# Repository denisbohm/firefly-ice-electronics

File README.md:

firefly-ice-electronics
=======================

Firefly Ice Activity Monitor / Internet of Things Electronics

See http://fireflydesign.com for information on the open source Firefly Activity Monitor.

Copyright and License 
---------------------
Copyright 2013-2014 Firefly Design LLC / Denis Bohm

<br />This work is licensed under a <a rel="license" href="http://creativecommons.org/licenses/by/3.0/deed.en_US">Creative Commons Attribution 3.0 Unported License</a>.

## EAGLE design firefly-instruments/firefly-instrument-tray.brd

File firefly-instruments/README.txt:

Contact: Denis Bohm
denis@fireflydesign.com
(650) 814-1714

April 13h, 2017
Customer: Firefly Design, LLC
Board: Firefly Instrument Tray rev 0.5
Number of Layers: 2
Dimensions: 193 mm x 100 mm
PCB Thickness: 1.60 mm
ENIG
RoHS Compliant
Lead Free Processing

Files

firefly-instrument-tray.sch - Eagle 7 schematic file
firefly-instrument-tray.brd - Eagle 7 board file

firefly-instrument-tray-bom.xlsx - bill of materials
firefly-instrument-tray-schematic.pdf - schematic
firefly-instrument-tray-top-diagram.pdf - top (component) side assembly diagram
firefly-instrument-tray-centroid.csv - surface mount centroid placement data

Gerbers
firefly-instrument-tray.top - top (component) side
firefly-instrument-tray.bot - bottom side

firefly-instrument-tray.slk - top (component) side silk
firefly-instrument-tray.smt - top (component) side solder mask
firefly-instrument-tray.tsp - top (component) side stencil

firefly-instrument-tray.bsk - bottom side silk
firefly-instrument-tray.smb - bottom side solder mask
firefly-instrument-tray.bsp - bottom side stencil

firefly-instrument-tray.oln - outline

firefly-instrument-tray.drd - Excellon drill
firefly-instrument-tray.dri - tool list

Notes:
1) The design is done with Eagle 7.7.0 (files are of type sch, brd, and lib)..
2) Use Firefly Design BOM tool to generate the BOM from the schematic.
3) The tDocu & Document layers show all reference designators and orientation for assembly of the top side.
4) The bDocu shows all reference designators and orientation for assembly of the bottom side.
5) DRC rules and CAM setup are from Sunstone Circuits.  For CAM setup use _tsilk for top side silk and _bsilk for bottom side silk.
6) Centroid file generator is from Screaming Circuits.

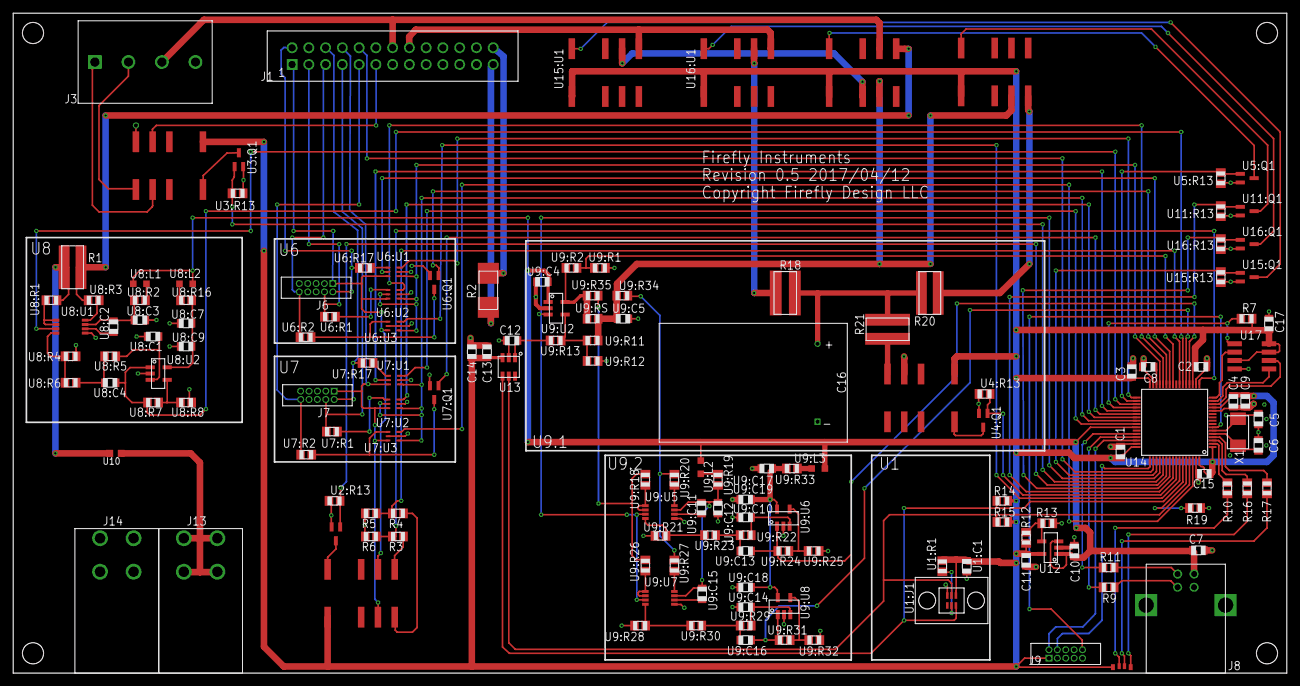
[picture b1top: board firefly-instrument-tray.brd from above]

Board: 2 copper layers, 193.0 x 100.0 mm, 153 parts (0 on the bottom side), 129 nets.

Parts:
C1, C2, C3, C12, C13, C15, C17: 100nF; C0805
C4, C10, C11: 1uF; C0805
C5, C6: 22pF; C0805
C7, C8: 4.7uF; C0805
C9: 10nF; C0805
C14: 10uF; C0805
C16: 1F; PM118
D1: LED-RGB-CAMSL0201RGB; MSL0201RGB
J1: CON-26; CON-HEADER-2X13
J3: CON-4282847-4; 282847-4
J6, J7, J9: CON-10SWD; SWD-10
J8: USB-4PINUSB-B1HSB6; USB-B1HSB6
J13, J14: CON-1CT3151; CT3151
R1: 0.1; KRL6432
R2: 100; RW0S6BB
R3, R4, R5, R6: 1k; R0805
R7: 10k; R0805
R9, R11: 22; R0805
R10, R16: 60; R0805
R12: 72.5k; R0805
R13: 10K; R0805
R14, R15: 4.7k; R0805
R17: 240; R0805
R18: 1 (2W WW); RCL1225
R19: 0; R0805
R20: 49.9 (2W WW); KRL6432
R21: 49.9 (2W WW); RCL1225
U1:C1, U8:C7, U9:C4, U9:C5, U9:C17: 1uF; C0805
U1:J1: SMFLP
U1:R1, U8:R5, U8:R6, U9:R22, U9:R23, U9:R29, U9:R30: 10k; R0805
U1:U1: TCS3471; DFN6
U2:Q1, U3:Q1, U4:Q1, U5:Q1, U6:Q1, U7:Q1, U11:Q1, U15:Q1, U16:Q1: FET-NMCPH3; MCPH3
U2:R13, U3:R13, U4:R13, U5:R13, U9:R28, U11:R13, U15:R13, U16:R13: 10K; R0805
U2:U1, U3:U1, U4:U1, U5:U1, U11:U1, U15:U1, U16:U1: TXS2SA
U6:R1, U6:R2, U6:R17, U7:R1, U7:R2, U7:R17: 240; R0805
U6:U1, U6:U2, U6:U3, U7:U1, U7:U2, U7:U3: 74LVCH1T45; SOT363
U8:C1, U8:C4, U9:C10, U9:C13, U9:C14, U9:C16: 1nF; C0805
U8:C2, U8:C9, U9:C11, U9:C15, U9:C18, U9:C19: 100nF; C0805
U8:C3, U9:C12: 10uF; C0805
U8:L1, U8:L2, U9:L2, U9:L3: 1k; L2012C
U8:R1, U9:R18: 1.8K; R0805
U8:R2, U9:R19, U9:R27, U9:R31, U9:R34, U9:R35: 0; R0805
U8:R3, U9:R20: 43; R0805
U8:R4, U9:R21: 12K; R0805
U8:R7, U9:R24: 376; R0805
U8:R8, U9:R25, U9:R32: 1K; R0805
U8:R16, U9:R33: 1; R0805
U8:U1, U9:U5, U9:U7: LTC6102-1MS8; MSOP8
U8:U2, U9:U6, U9:U8: TLV271SN2T1G; SOT-23-5
U9:R1, U9:R2, U9:R12, U9:R13: 100K; R0805
U9:R11: 650K; R0805
U9:R26, U9:RS: 4.7; R0805
U9:U2, U12: VREG-ADJAP7331-WG-7; SOT-23-5
U10: PTC0603; 0603
U13: MCP47X6; SOT-23-6
U14: STM32F411-LQFP64; LQFP-64
U17: MEMORY-SPISOA008; SOA008
X1: XTAL2CX5032GA; CX5032GA

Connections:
+3V3: C1.1, C2.1, C3.1, C4.1, C9.1, C11.1, C13.1, C14.1, C15.1, C17.1, D1.4, J9.1, R7.2, R12.2, R14.2, R15.2, U1:C1.1, U1:R1.2, U1:U1.1, U2:U1.1, U3:U1.1, U4:U1.1, U5:U1.1, U11:U1.1, U12.5, U13.3, U14.1, U14.13, U14.19, U14.32, U14.48, U14.64, U15:U1.1, U16:U1.1, U17.3, U17.7, U17.8
+5V: J13.1, J13.2, J13.3, J13.4, U10.1
ATE_BATTERY+2: U9:R1.2, U9:R2.1, U14.25
ATE_BAT_ADJ_EN: U14.51, U15:Q1.1, U15:R13.2
ATE_BAT_CAP_EN: U14.55, U16:Q1.1, U16:R13.2
ATE_BS_ADJ: C12.1, U9:R13.1, U13.1
ATE_BS_EN: U9:U2.3, U9:U5.3, U9:U7.3, U14.52
ATE_BS_SHR: U9:C13.1, U9:R24.2, U9:U6.1, U14.20
ATE_BS_SLR: U9:C16.1, U9:R31.2, U9:U8.1, U14.21
ATE_BUTTON_EN: U3:Q1.1, U3:R13.2, U14.53
ATE_DRAIN_EN: U4:Q1.1, U4:R13.2, U14.57
ATE_FILL_EN: U11:Q1.1, U11:R13.2, U14.56
ATE_MCU1_VCC2: R3.2, R6.1, U14.17
ATE_MCU2_VCC2: R4.2, R5.1, U14.23
ATE_MCU_VCC_SENSE: U2:Q1.1, U2:R13.2, U14.54
ATE_SCL: R15.1, U1:U1.2, U13.5, U14.61
ATE_SDA: R14.1, U1:U1.6, U13.4, U14.59
ATE_SWD1_DIR_TO_DUT: U6:U1.5, U14.26
ATE_SWD1_NRESET: U6:Q1.1, U14.27
ATE_SWD1_PWR: U6:U1.1, U6:U2.1, U6:U2.5, U6:U3.1, U14.29
ATE_SWD1_SENSE_NRESET: U6:U3.3, U14.58
ATE_SWD1_SWDCLK: U6:U2.3, U14.28
ATE_SWD1_SWDIO: U6:U1.3, U14.33
ATE_SWD2_DIR_TO_DUT: U7:U1.5, U14.37
ATE_SWD2_NRESET: U7:Q1.1, U14.38
ATE_SWD2_PWR: U7:U1.1, U7:U2.1, U7:U2.5, U7:U3.1, U14.40
ATE_SWD2_SENSE_NRESET: U7:U3.3, U14.62
ATE_SWD2_SWDCLK: U7:U2.3, U14.39
ATE_SWD2_SWDIO: U7:U1.3, U14.41
ATE_USB_5V_EN: U5:Q1.1, U5:R13.2, U14.34
ATE_USB_CS_EN: U8:U1.3, U14.35
ATE_USB_CS_OUT: U8:C4.1, U8:R7.2, U8:U2.1, U14.22
BATADJ: U5:U1.4, U9:C5.1, U9:R11.2, U9:R34.2, U9:RS.2, U11:U1.4
BATADJSAFE: U5:U1.3, U15:U1.9
BATCAP: R18.1, U16:U1.9
BOOT0: R19.1, U14.60
DRAINCAP: R21.1, U4:U1.5
DUT_BATTERY+: J1.16, U15:U1.8, U16:U1.8
DUT_BUTTON+: J1.11, U3:U1.4
DUT_MCU1_NRESET: J1.5, J6.10, U6:R2.2
DUT_MCU1_SWDCLK: J1.3, J6.4, U6:R1.2
DUT_MCU1_SWDIO: J1.2, J6.2, U6:R17.2
DUT_MCU1_VCC: J1.1, J6.1, U2:U1.9, U6:U1.6, U6:U2.6, U6:U3.6
DUT_MCU2_BOOT0: J1.10, U14.50
DUT_MCU2_NRESET: J1.9, J7.10, U7:R2.2
DUT_MCU2_SWDCLK: J1.7, J7.4, U7:R1.2
DUT_MCU2_SWDIO: J1.6, J7.2, U7:R17.2
DUT_MCU2_VCC: J1.8, J7.1, U2:U1.4, U7:U1.6, U7:U2.6, U7:U3.6
DUT_MOTOR+: J1.26, R2.1
DUT_MOTOR-: J1.25, R2.2
DUT_SWITCH_1: J3.1, U3:U1.9
DUT_SWITCH_2: J3.2, U3:U1.8
DUT_USB_5V: J1.14, J3.3, U5:U1.9
FILLCAP: R20.1, U11:U1.5
GND: C1.2, C2.2, C3.2, C4.2, C5.2, C6.2, C7.2, C8.2, C9.2, C10.2, C11.2, C12.2, C13.2, C14.2, C15.2, C16.-, C17.2, J1.4, J1.23, J1.24, J3.4, J6.3, J6.5, J7.3, J7.5, J8.4, J9.3, J9.5, J14.1, J14.2, J14.3, J14.4, R5.2, R6.2, R13.1, R19.2, U1:C1.2, U1:U1.3, U2:Q1.2, U2:R13.1, U3:Q1.2, U3:R13.1, U3:U1.5, U4:Q1.2, U4:R13.1, U4:U1.4, U5:Q1.2, U5:R13.1, U6:Q1.2, U6:U1.2, U6:U2.2, U6:U3.2, U6:U3.5, U7:Q1.2, U7:U1.2, U7:U2.2, U7:U3.2, U7:U3.5, U8:C1.2, U8:C3.2, U8:C7.2, U8:C9.2, U8:R4.2, U8:R8.2, U8:U1.5, U8:U2.2, U9:C4.2, U9:C5.2, U9:C10.2, U9:C12.2, U9:C14.2, U9:C17.2, U9:C18.2, U9:C19.2, U9:R1.1, U9:R12.1, U9:R21.2, U9:R25.2, U9:R28.2, U9:R32.2, U9:U2.2, U9:U5.5, U9:U6.2, U9:U7.5, U9:U8.2, U11:Q1.2, U11:R13.1, U12.2, U13.2, U14.12, U14.18, U14.31, U14.47, U14.63, U15:Q1.2, U15:R13.1, U16:Q1.2, U16:R13.1, U17.4
MEM_CSN: R7.1, U14.36, U17.1
unnamed: R10.2, U14.2
unnamed: R1.2, U5:U1.8, U8:R3.1
unnamed: R1.1, U8:R1.2, U10.2
unnamed: C16.+, R18.2, R20.2, R21.2
unnamed: C5.1, U14.6, X1.2
unnamed: C6.1, U14.5, X1.1
unnamed: R16.2, U14.3
unnamed: R4.1, U2:U1.5
unnamed: R3.1, U2:U1.8
unnamed: C8.1, U14.30
unnamed: R12.1, R13.2, U12.4
unnamed: J8.2, R11.2
unnamed: R17.2, U14.4
unnamed: J8.3, R9.2
unnamed: D1.3, R10.1
unnamed: D1.1, R16.1
unnamed: D1.2, R17.1
NRESET: J9.10, U14.7
SPI_MISO: U14.16, U17.2
SPI_MOSI: U14.15, U17.5
SPI_SCLK: U14.14, U17.6
SWCLK: J9.4, U14.49
SWDIO: J9.2, U14.46
U1:INT: U1:R1.1, U1:U1.5
U2:N$2: U2:Q1.3, U2:U1.12
U3:N$2: U3:Q1.3, U3:U1.12
U4:N$2: U4:Q1.3, U4:U1.12
U5:N$2: U5:Q1.3, U5:U1.12
U6:N$1: U6:Q1.3, U6:R2.1, U6:U3.4
U6:N$2: U6:R17.1, U6:U1.4
U6:N$3: U6:R1.1, U6:U2.4
U7:N$1: U7:Q1.3, U7:R2.1, U7:U3.4
U7:N$2: U7:R17.1, U7:U1.4
U7:N$3: U7:R1.1, U7:U2.4
U8:N$1: U8:L1.2, U8:R2.2
U8:N$2: U8:L2.2, U8:R16.2
U8:N$3: U8:C2.1, U8:U1.6
U8:N$4: U8:R1.1, U8:U1.1, U8:U1.2
U8:N$7: U8:R3.2, U8:U1.8
U8:N$9: U8:R4.1, U8:R6.1, U8:U1.4
U8:N$10: U8:C4.2, U8:R5.1, U8:R6.2
U8:N$11: U8:C1.1, U8:R5.2, U8:U2.3
U8:N$12: U8:R7.1, U8:R8.1, U8:U2.4
U8:VCSA: U8:C2.2, U8:C3.1, U8:R2.1, U8:U1.7
U8:VOA: U8:C7.1, U8:C9.1, U8:R16.1, U8:U2.5
U9:N$4: U9:R11.1, U9:R12.2, U9:R13.2, U9:U2.4
U9:N$13: U9:L2.2, U9:R19.2
U9:N$14: U9:C11.1, U9:U5.6
U9:N$15: U9:R18.1, U9:U5.1, U9:U5.2
U9:N$16: U9:R20.2, U9:U5.8
U9:N$17: U9:R21.1, U9:R23.1, U9:U5.4
U9:N$18: U9:C13.2, U9:R22.1, U9:R23.2
U9:N$19: U9:C10.1, U9:R22.2, U9:U6.3
U9:N$20: U9:R24.1, U9:R25.1, U9:U6.4
U9:N$21: U9:C15.1, U9:U7.6
U9:N$22: U9:R26.1, U9:U7.1, U9:U7.2
U9:N$23: U9:R27.2, U9:U7.8
U9:N$24: U9:R28.1, U9:R30.1, U9:U7.4
U9:N$25: U9:C16.2, U9:R29.1, U9:R30.2
U9:N$26: U9:C14.1, U9:R29.2, U9:U8.3
U9:N$27: U9:R31.1, U9:R32.1, U9:U8.4
U9:N$28: U9:L3.2, U9:R33.2
U9:N$35: U9:R2.2, U9:R35.2, U9:RS.1, U9:U2.5
U9:SENSE_R: U9:R18.2, U9:R26.2, U9:R35.1
U9:SENSE_S: U9:R20.1, U9:R27.1, U9:R34.1
U9:VCSA: U9:C11.2, U9:C12.1, U9:C15.2, U9:R19.1, U9:U5.7, U9:U7.7
U9:VOA: U9:C17.1, U9:C18.1, U9:C19.1, U9:R33.1, U9:U6.5, U9:U8.5
U11:N$2: U11:Q1.3, U11:U1.12
U15:N$2: U15:Q1.3, U15:U1.12
U16:N$2: U16:Q1.3, U16:U1.12
USB_DM: R11.1, U14.44
USB_DP: R9.1, U14.45
USB_VBUS: C7.1, C10.1, J8.1, U8:L1.1, U8:L2.1, U9:C4.1, U9:L2.1, U9:L3.1, U9:U2.1, U12.1, U12.3, U14.42

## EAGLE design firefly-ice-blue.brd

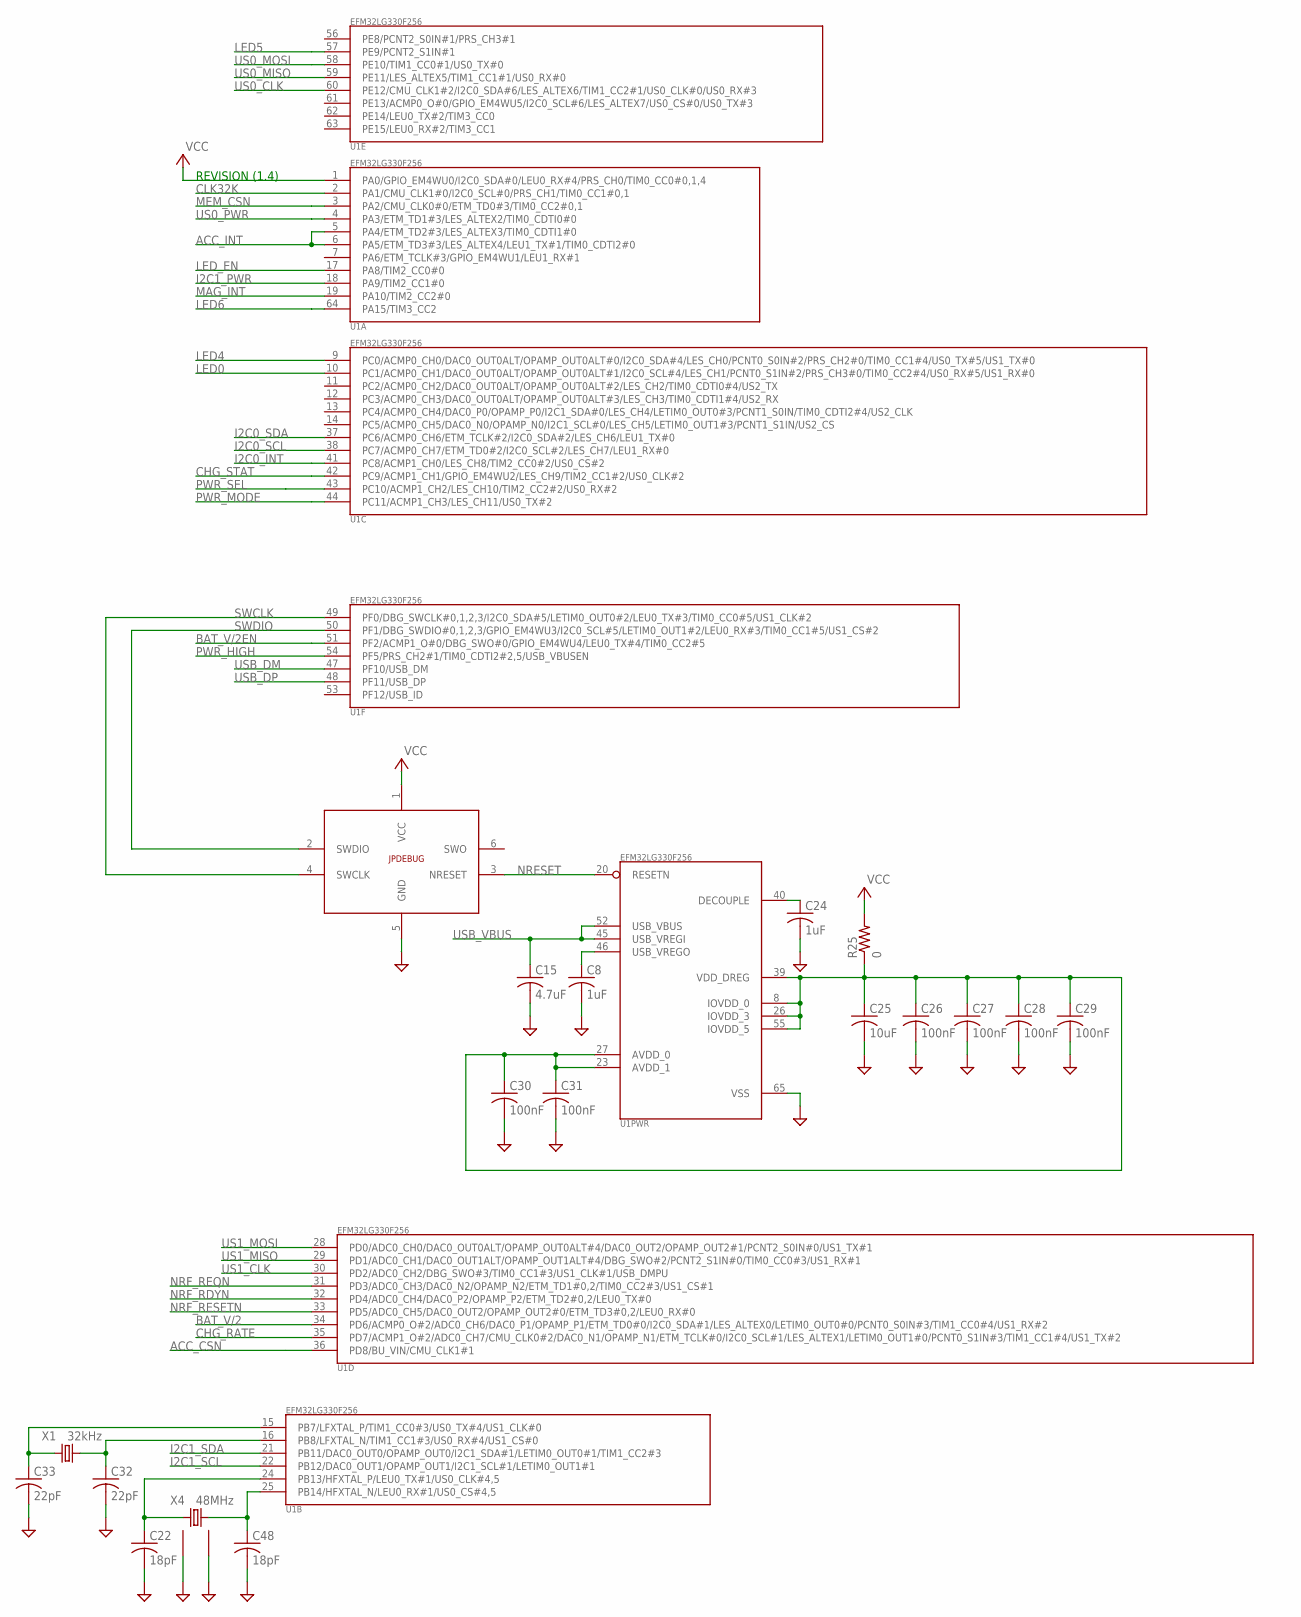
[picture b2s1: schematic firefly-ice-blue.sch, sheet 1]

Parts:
C8, C24: 1uF; C0201
C15: 4.7uF; C0402
C22, C48: 18pF; C0201
C25: 10uF; C0402
C26, C27, C28, C29, C30, C31: 100nF; C0201
C32, C33: 22pF; C0201
JPDEBUG: TC2030-SWD; TC2030-MCP-NL
R25: 0; R0201
U1: EFM32LG330F256; QFN64
X1: 32kHz; 9HT10
X4: 48MHz; ABM11

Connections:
ACC_CSN: U1.36 (PD8/BU_VIN/CMU_CLK1#1); also elsewhere on the board
ACC_INT: U1.5 (PA4/ETM_TD2#3/LES_ALTEX3/TIM0_CDTI1#0), U1.6 (PA5/ETM_TD3#3/LES_ALTEX4/LEU1_TX#1/TIM0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); also elsewhere on the board
BAT_V/2: U1.34 (PD6/ACMP0_O#2/ADC0_CH6/DAC0_P1/OPAMP_P1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); also elsewhere on the board
BAT_V/2EN: U1.51 (PF2/ACMP1_O#0/DBG_SWO#0/GPIO_EM4WU4/LEU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); also elsewhere on the board
CHG_RATE: U1.35 (PD7/ACMP1_O#2/ADC0_CH7/CMU_CLK0#2/DAC0_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); also elsewhere on the board
CHG_STAT: U1.42 (PC9/ACMP1_CH1/GPIO_EM4WU2/LES_CH9/TIM2_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); also elsewhere on the board
CLK32K: U1.2 (PA1/CMU_CLK1#0/I2C0_SCL#0/PRS_CH1/TIM0_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); also elsewhere on the board
GND: C8.2, C15.2, C22.2, C24.2, C25.2, C26.2, C27.2, C28.2, C29.2, C30.2, C31.2, C32.2, C33.2, C48.2, JPDEBUG.5 (GND), U1.65 (VSS), X4.2 (GND1), X4.4 (GND2); also elsewhere on the board
I2C0_INT: U1.41 (PC8/ACMP1_CH0/LES_CH8/TIM2_CC0#2/US0_CS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); also elsewhere on the board
I2C0_SCL: U1.38 (PC7/ACMP0_CH7/ETM_TD0#2/I2C0_SCL#2/LES_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); also elsewhere on the board
I2C0_SDA: U1.37 (PC6/ACMP0_CH6/ETM_TCLK#2/I2C0_SDA#2/LES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); also elsewhere on the board
I2C1_PWR: U1.18 (PA9/TIM2_CC1#0); also elsewhere on the board
I2C1_SCL: U1.22 (PB12/DAC0_OUT1/OPAMP_OUT1/I2C1_SCL#1/LE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); also elsewhere on the board
I2C1_SDA: U1.21 (PB11/DAC0_OUT0/OPAMP_OUT0/I2C1_SDA#1/LE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); also elsewhere on the board
LED0: U1.10 (PC1/ACMP0_CH1/DAC0_OUT0ALT/OPAMP_OUT0AL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); also elsewhere on the board
LED4: U1.9 (PC0/ACMP0_CH0/DAC0_OUT0ALT/OPAMP_OUT0AL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); also elsewhere on the board
LED5: U1.57 (PE9/PCNT2_S1IN#1); also elsewhere on the board
LED6: U1.64 (PA15/TIM3_CC2); also elsewhere on the board
LED_EN: U1.17 (PA8/TIM2_CC0#0); also elsewhere on the board
MAG_INT: U1.19 (PA10/TIM2_CC2#0); also elsewhere on the board
MEM_CSN: U1.3 (PA2/CMU_CLK0#0/ETM_TD0#3/TIM0_CC2#0,1); also elsewhere on the board
unnamed: C8.1, U1.46 (USB_VREGO)
unnamed: C48.1, U1.25 (PB14/HFXTAL_N/LEU0_RX#1/US0_CS#4,5), X4.3 (2)
unnamed: C24.1, U1.40 (DECOUPLE)
unnamed: C33.1, U1.15 (PB7/LFXTAL_P/TIM1_CC0#3/US0_TX#4/US1_CL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), X1.1
unnamed: C22.1, U1.24 (PB13/HFXTAL_P/LEU0_TX#1/US0_CLK#4,5), X4.1
unnamed: C32.1, U1.16 (PB8/LFXTAL_N/TIM1_CC1#3/US0_RX#4/US1_CS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), X1.2
unnamed: C25.1, C26.1, C27.1, C28.1, C29.1, C30.1, C31.1, R25.1, U1.8 (IOVDD_0), U1.23 (AVDD_1), U1.26 (IOVDD_3), U1.27 (AVDD_0), U1.39 (VDD_DREG), U1.55 (IOVDD_5)
NRESET: JPDEBUG.3 (NRESET), U1.20 (RESETN); also elsewhere on the board
NRF_RDYN: U1.32 (PD4/ADC0_CH4/DAC0_P2/OPAMP_P2/ETM_TD2#0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); also elsewhere on the board
NRF_REQN: U1.31 (PD3/ADC0_CH3/DAC0_N2/OPAMP_N2/ETM_TD1#0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); also elsewhere on the board
NRF_RESETN: U1.33 (PD5/ADC0_CH5/DAC0_OUT2/OPAMP_OUT2#0/ETM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); also elsewhere on the board
PWR_HIGH: U1.54 (PF5/PRS_CH2#1/TIM0_CDTI2#2,5/USB_VBUSEN); also elsewhere on the board
PWR_MODE: U1.44 (PC11/ACMP1_CH3/LES_CH11/US0_TX#2); also elsewhere on the board
PWR_SEL: U1.43 (PC10/ACMP1_CH2/LES_CH10/TIM2_CC2#2/US0_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); also elsewhere on the board
SWCLK: JPDEBUG.4 (SWCLK), U1.49 (PF0/DBG_SWCLK#0,1,2,3/I2C0_SDA#5/LETIM0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)
SWDIO: JPDEBUG.2 (SWDIO), U1.50 (PF1/DBG_SWDIO#0,1,2,3/GPIO_EM4WU3/I2C0_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)
US0_CLK: U1.60 (PE12/CMU_CLK1#2/I2C0_SDA#6/LES_ALTEX6/T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); also elsewhere on the board
US0_MISO: U1.59 (PE11/LES_ALTEX5/TIM1_CC1#1/US0_RX#0); also elsewhere on the board
US0_MOSI: U1.58 (PE10/TIM1_CC0#1/US0_TX#0); also elsewhere on the board
US0_PWR: U1.4 (PA3/ETM_TD1#3/LES_ALTEX2/TIM0_CDTI0#0); also elsewhere on the board
US1_CLK: U1.30 (PD2/ADC0_CH2/DBG_SWO#3/TIM0_CC1#3/US1_C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); also elsewhere on the board
US1_MISO: U1.29 (PD1/ADC0_CH1/DAC0_OUT1ALT/OPAMP_OUT1ALT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); also elsewhere on the board
US1_MOSI: U1.28 (PD0/ADC0_CH0/DAC0_OUT0ALT/OPAMP_OUT0ALT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); also elsewhere on the board
USB_DM: U1.47 (PF10/USB_DM); also elsewhere on the board
USB_DP: U1.48 (PF11/USB_DP); also elsewhere on the board
USB_VBUS: C15.1, U1.45 (USB_VREGI), U1.52 (USB_VBUS); also elsewhere on the board
VCC: JPDEBUG.1 (VCC), R25.2, U1.1 (PA0/GPIO_EM4WU0/I2C0_SDA#0/LEU0_RX#4/PR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); also elsewhere on the board

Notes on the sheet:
REVISION (1.4)

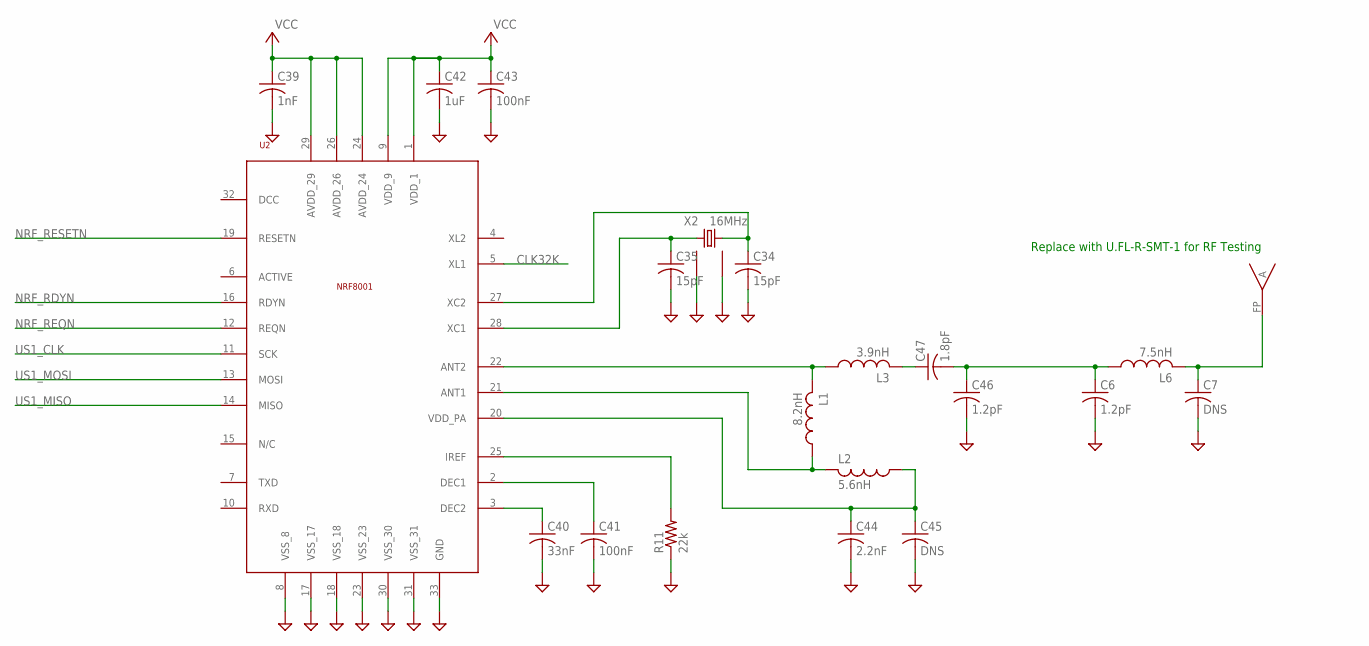
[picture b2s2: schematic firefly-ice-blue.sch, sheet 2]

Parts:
A1: FR05_S1_N_0_110
C6, C46: 1.2pF; C0201
C7, C45: DNS; C0201
C34, C35: 15pF; C0201
C39: 1nF; C0201
C40: 33nF; C0201
C41, C43: 100nF; C0201
C42: 1uF; C0201
C44: 2.2nF; C0201
C47: 1.8pF; C0201
L1: 8.2nH; L0201
L2: 5.6nH; L0201
L3: 3.9nH; L0201
L6: 7.5nH; L0201
R11: 22k; R0201
U2: NRF8001; QFN-32
X2: 16MHz; XTAL2520

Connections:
CLK32K: U2.5 (XL1); also elsewhere on the board
GND: C6.2, C7.2, C34.2, C35.2, C39.2, C40.2, C41.2, C42.2, C43.2, C44.2, C45.2, C46.2, R11.1, U2.8 (VSS_8), U2.17 (VSS_17), U2.18 (VSS_18), U2.23 (VSS_23), U2.30 (VSS_30), U2.31 (VSS_31), U2.33 (GND), X2.2 (GND1), X2.4 (GND2); also elsewhere on the board
unnamed: A1.FP, C7.1, L6.2
unnamed: C35.1, U2.28 (XC1), X2.1
unnamed: C34.1, U2.27 (XC2), X2.3 (2)
unnamed: R11.2, U2.25 (IREF)
unnamed: C40.1, U2.3 (DEC2)
unnamed: C41.1, U2.2 (DEC1)
unnamed: C47.1, L3.2
unnamed: C6.1, C46.1, C47.2, L6.1
unnamed: C44.1, C45.1, L2.1, U2.20 (VDD_PA)
unnamed: L1.1, L2.2, U2.21 (ANT1)
unnamed: L1.2, L3.1, U2.22 (ANT2)
NRF_RDYN: U2.16 (RDYN); also elsewhere on the board
NRF_REQN: U2.12 (REQN); also elsewhere on the board
NRF_RESETN: U2.19 (RESETN); also elsewhere on the board
US1_CLK: U2.11 (SCK); also elsewhere on the board
US1_MISO: U2.14 (MISO); also elsewhere on the board
US1_MOSI: U2.13 (MOSI); also elsewhere on the board
VCC: C39.1, C42.1, C43.1, U2.1 (VDD_1), U2.9 (VDD_9), U2.24 (AVDD_24), U2.26 (AVDD_26), U2.29 (AVDD_29); also elsewhere on the board

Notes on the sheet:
Replace with U.FL-R-SMT-1 for RF Testing

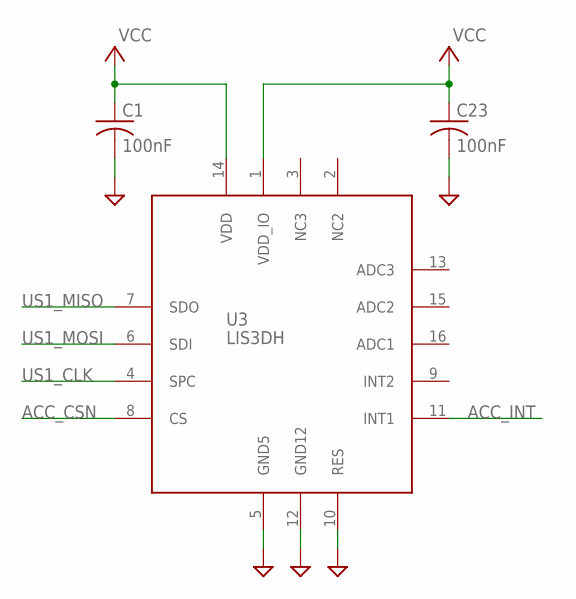
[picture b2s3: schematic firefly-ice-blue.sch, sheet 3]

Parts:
C1, C23: 100nF; C0201
U3: LIS3DH; LGA16_3X3

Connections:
ACC_CSN: U3.8 (CS); also elsewhere on the board
ACC_INT: U3.11 (INT1); also elsewhere on the board
GND: C1.2, C23.2, U3.5 (GND5), U3.10 (RES), U3.12 (GND12); also elsewhere on the board
US1_CLK: U3.4 (SPC); also elsewhere on the board
US1_MISO: U3.7 (SDO); also elsewhere on the board
US1_MOSI: U3.6 (SDI); also elsewhere on the board
VCC: C1.1, C23.1, U3.1 (VDD_IO), U3.14 (VDD); also elsewhere on the board

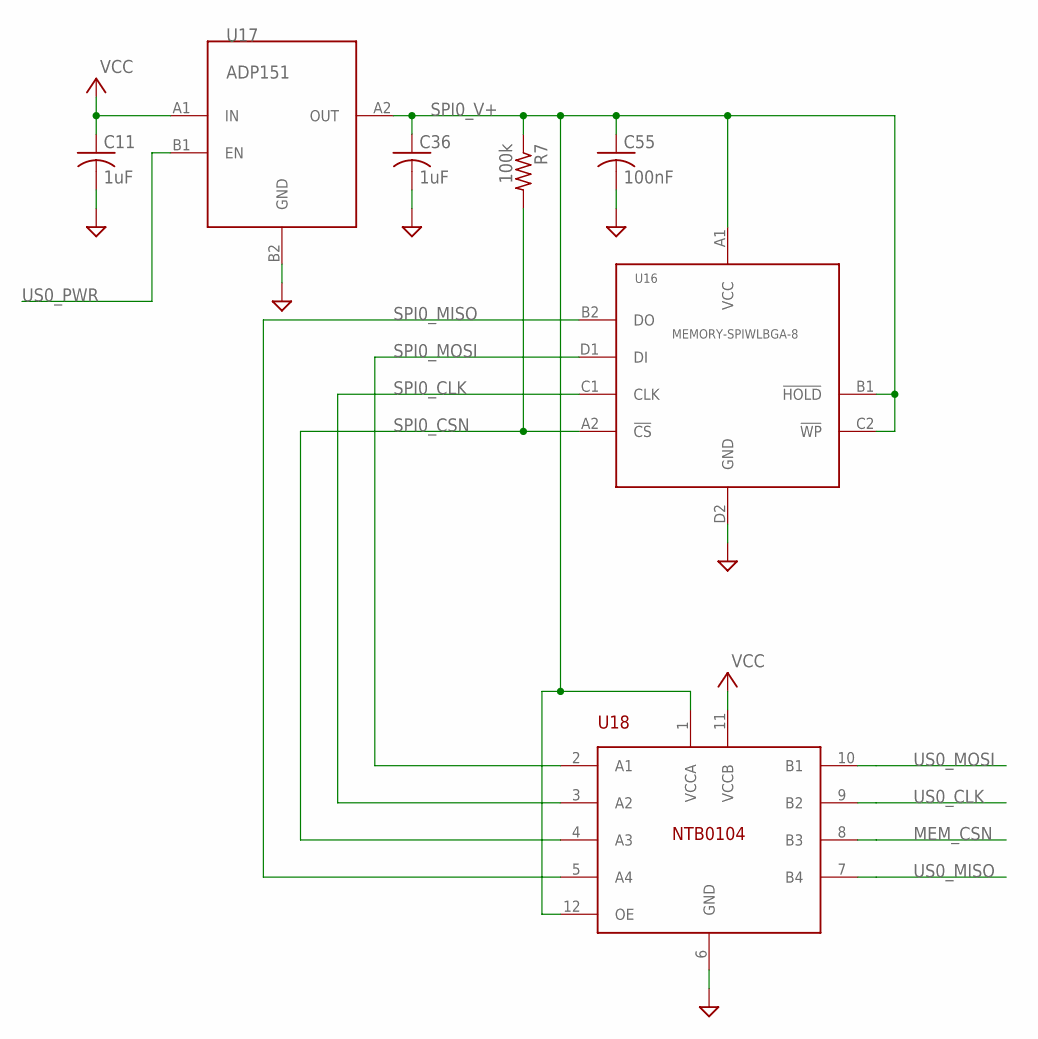
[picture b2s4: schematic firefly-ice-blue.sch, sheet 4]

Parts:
C11, C36: 1uF; C0201
C55: 100nF; C0201
R7: 100k; R0201
U16: MEMORY-SPIWLBGA-8; WLBGA-8
U17: ADP151; CB-4-3
U18: NTB0104; XQFN12

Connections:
GND: C11.2, C36.2, C55.2, U16.D2 (GND), U17.B2 (GND), U18.6 (GND); also elsewhere on the board
MEM_CSN: U18.8 (B3); also elsewhere on the board
SPI0_CLK: U16.C1 (CLK), U18.3 (A2)
SPI0_CSN: R7.2, U16.A2 (!CS), U18.4 (A3)
SPI0_MISO: U16.B2 (DO), U18.5 (A4)
SPI0_MOSI: U16.D1 (DI), U18.2 (A1)
SPI0_V+: C36.1, C55.1, R7.1, U16.A1 (VCC), U16.B1 (!HOLD), U16.C2 (!WP), U17.A2 (OUT), U18.1 (VCCA), U18.12 (OE)
US0_CLK: U18.9 (B2); also elsewhere on the board
US0_MISO: U18.7 (B4); also elsewhere on the board
US0_MOSI: U18.10 (B1); also elsewhere on the board
US0_PWR: U17.B1 (EN); also elsewhere on the board
VCC: C11.1, U17.A1 (IN), U18.11 (VCCB); also elsewhere on the board

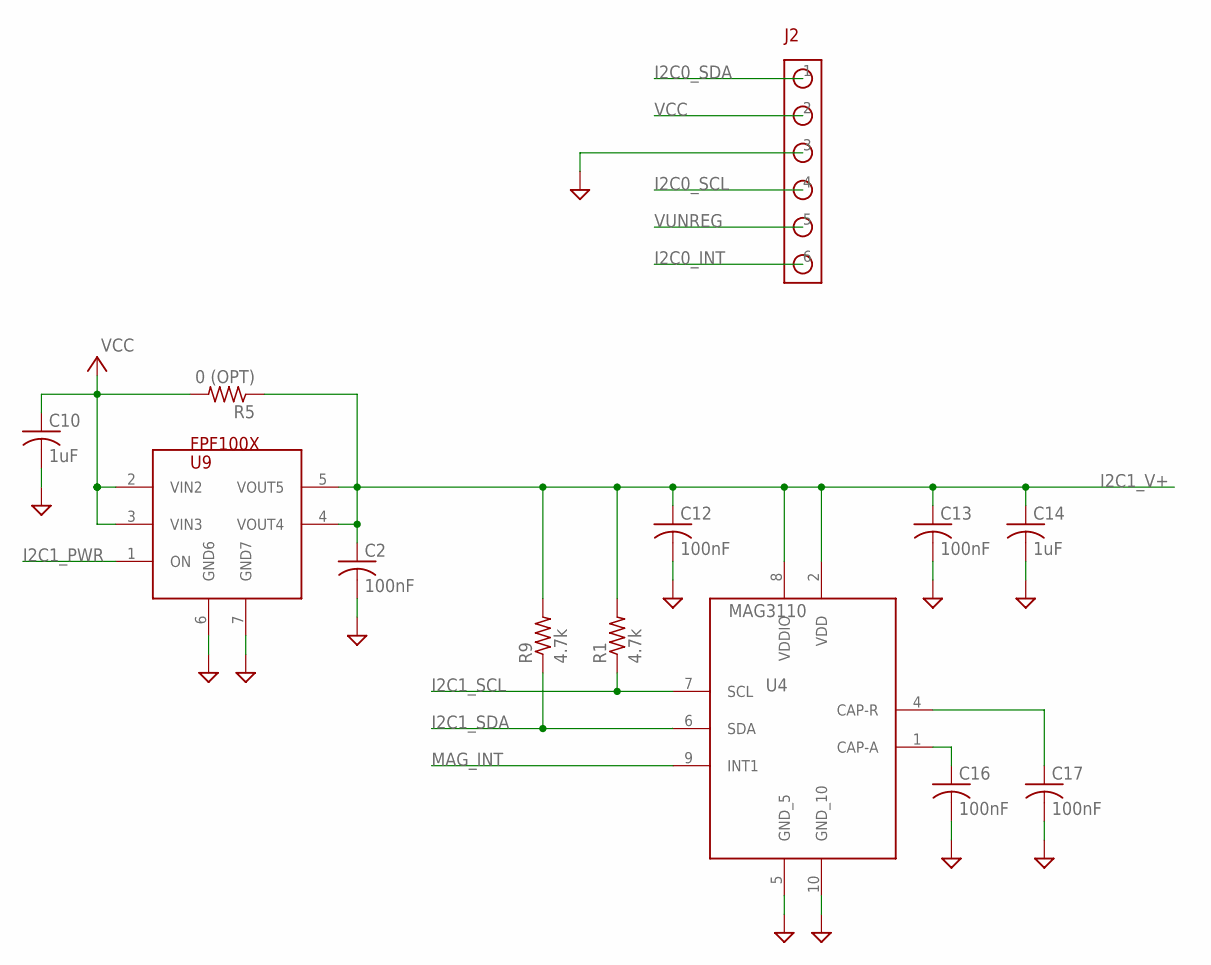
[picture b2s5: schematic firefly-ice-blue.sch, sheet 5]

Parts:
C2, C12, C13, C16, C17: 100nF; C0201
C10, C14: 1uF; C0201
J2: CON-6SOCKET; M40-3100345R
R1, R9: 4.7k; R0201
R5: 0 (OPT); R0201
U4: MAG3110; DFN10-2X2
U9: FPF100X; MICROFET-2X2-6L

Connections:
GND: C2.2, C10.2, C12.2, C13.2, C14.2, C16.2, C17.2, J2.3, U4.5 (GND_5), U4.10 (GND_10), U9.6 (GND6), U9.7 (GND7); also elsewhere on the board
I2C0_INT: J2.6; also elsewhere on the board
I2C0_SCL: J2.4; also elsewhere on the board
I2C0_SDA: J2.1; also elsewhere on the board
I2C1_PWR: U9.1 (ON); also elsewhere on the board
I2C1_SCL: R1.1, U4.7 (SCL); also elsewhere on the board
I2C1_SDA: R9.1, U4.6 (SDA); also elsewhere on the board
I2C1_V+: C2.1, C12.1, C13.1, C14.1, R1.2, R5.1, R9.2, U4.2 (VDD), U4.8 (VDDIO), U9.4 (VOUT4), U9.5 (VOUT5)
MAG_INT: U4.9 (INT1); also elsewhere on the board
unnamed: C16.1, U4.1 (CAP-A)
unnamed: C17.1, U4.4 (CAP-R)
VCC: C10.1, J2.2, R5.2, U9.2 (VIN2), U9.3 (VIN3); also elsewhere on the board
VUNREG: J2.5; also elsewhere on the board

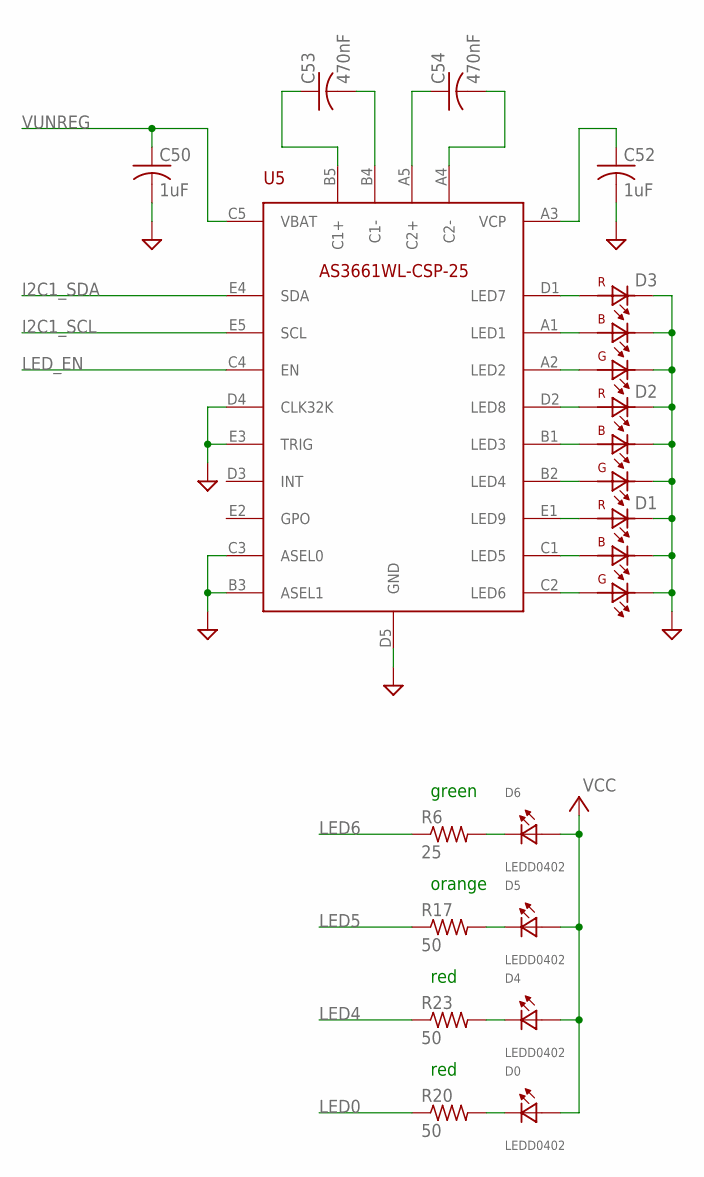
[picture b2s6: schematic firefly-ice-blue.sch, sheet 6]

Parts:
C50, C52: 1uF; C0201
C53, C54: 470nF; C0201
D0, D4, D5, D6: LEDD0402; D0402
D1, D2, D3: LED-RGB; SMLP36
R6: 25; R0201
R17, R20, R23: 50; R0201
U5: AS3661WL-CSP-25; WL-CSP-25

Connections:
GND: C50.2, C52.2, D1.1 (BC), D1.3 (RC), D1.5 (GC), D2.1 (BC), D2.3 (RC), D2.5 (GC), D3.1 (BC), D3.3 (RC), D3.5 (GC), U5.B3 (ASEL1), U5.C3 (ASEL0), U5.D4 (CLK32K), U5.D5 (GND), U5.E3 (TRIG); also elsewhere on the board
I2C1_SCL: U5.E5 (SCL); also elsewhere on the board
I2C1_SDA: U5.E4 (SDA); also elsewhere on the board
LED0: R20.1; also elsewhere on the board
LED4: R23.1; also elsewhere on the board
LED5: R17.1; also elsewhere on the board
LED6: R6.1; also elsewhere on the board
LED_EN: U5.C4 (EN); also elsewhere on the board
unnamed: D1.2 (BA), U5.C2 (LED6)
unnamed: C52.1, U5.A3 (VCP)
unnamed: C53.2, U5.B4 (C1-)
unnamed: D6.C, R6.2
unnamed: D5.C, R17.2
unnamed: D1.6 (GA), U5.C1 (LED5)
unnamed: D1.4 (RA), U5.E1 (LED9)
unnamed: D2.2 (BA), U5.B2 (LED4)
unnamed: D4.C, R23.2
unnamed: D0.C, R20.2
unnamed: C53.1, U5.B5 (C1+)
unnamed: D2.6 (GA), U5.B1 (LED3)
unnamed: D2.4 (RA), U5.D2 (LED8)
unnamed: D3.2 (BA), U5.A2 (LED2)
unnamed: C54.1, U5.A5 (C2+)
unnamed: D3.6 (GA), U5.A1 (LED1)
unnamed: C54.2, U5.A4 (C2-)
unnamed: D3.4 (RA), U5.D1 (LED7)
VCC: D0.A, D4.A, D5.A, D6.A; also elsewhere on the board
VUNREG: C50.1, U5.C5 (VBAT); also elsewhere on the board

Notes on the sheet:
green
orange
red

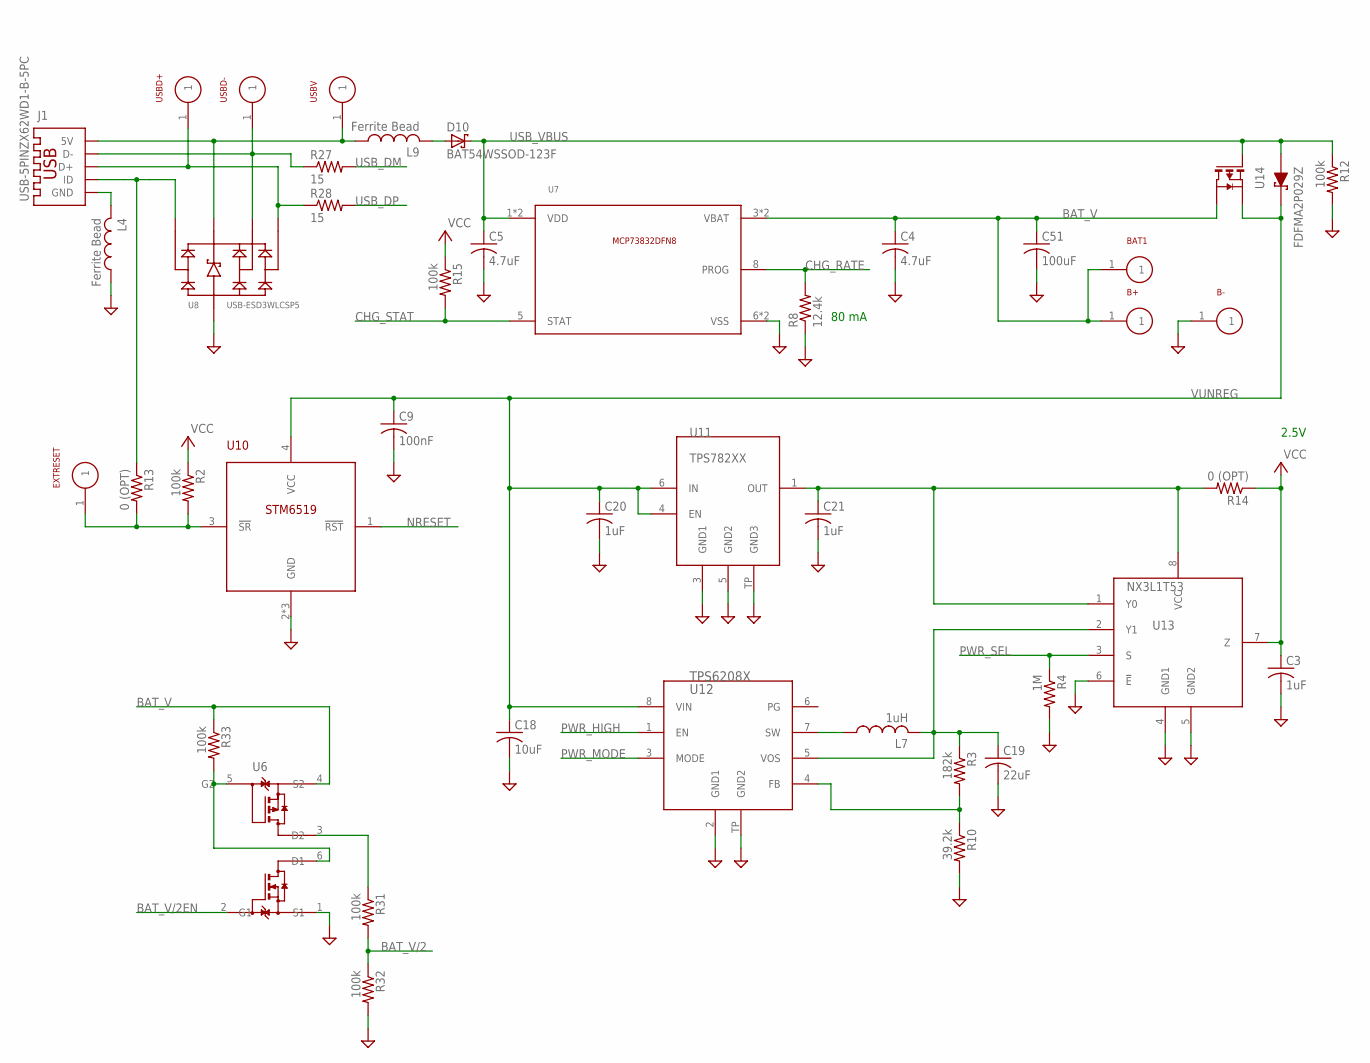
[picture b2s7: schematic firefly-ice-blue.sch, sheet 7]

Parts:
B+: TARGET-PINWP-28AWG; WP-28AWG
B-: TARGET-PINWP-28AWG; WP-28AWG
BAT1: TARGET-PIN; TARGET-PIN-1MM
C3, C20, C21: 1uF; C0201
C4, C5: 4.7uF; C0402
C9: 100nF; C0201
C18: 10uF; C0402
C19: 22uF; C0603
C51: 100uF; C1206
D10: BAT54WSSOD-123F; SOD-123F
EXTRESET: TARGET-PIN; TARGET-PIN-1MM
J1: USB-5PINZX62WD1-B-5PC; ZX62WD1-B-5PC
L4, L9: Ferrite Bead; L0201
L7: 1uH; L0805
R2, R12, R15, R31, R32, R33: 100k; R0201
R3: 182k; R0201
R4: 1M; R0201
R8: 12.4k; R0201
R10: 39.2k; R0201
R13, R14: 0 (OPT); R0201
R27, R28: 15; R0201
U6: MOSFET-N+PSOT963; SOT963
U7: MCP73832DFN8; DFN8
U8: USB-ESD3WLCSP5; WLCSP5
U10: STM6519; UDFN6
U11: TPS782XX; S-PWSON-N6
U12: TPS6208X; S-PWSON-N8
U13: NX3L1T53; SOT902-2
U14: FDFMA2P029Z; MO-229
USBD+: TARGET-PIN; TARGET-PIN-1MM
USBD-: TARGET-PIN; TARGET-PIN-1MM
USBV: TARGET-PIN; TARGET-PIN-1MM

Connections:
BAT_V: B+.1, BAT1.1, C4.1, C51.1, R33.1, U6.4 (S2), U7.3 (VBAT), U7.4 (VBAT), U14.3 (D)
BAT_V/2: R31.2, R32.1; also elsewhere on the board
BAT_V/2EN: U6.2 (G1); also elsewhere on the board
CHG_RATE: R8.2, U7.8 (PROG); also elsewhere on the board
CHG_STAT: R15.2, U7.5 (STAT); also elsewhere on the board
GND: B-.1, C3.2, C4.2, C5.2, C9.2, C18.2, C19.2, C20.2, C21.2, C51.2, L4.1, R4.2, R8.1, R10.2, R12.2, R32.2, U6.1 (S1), U7.6 (VSS), U7.PGND (VSS), U8.B1 (GND), U10.2 (GND), U10.5 (GND), U10.6 (GND), U11.3 (GND1), U11.5 (GND2), U11.TP (GND3), U12.2 (GND1), U12.TP (GND2), U13.4 (GND1), U13.5 (GND2), U13.6 (!E); also elsewhere on the board
unnamed: J1.5 (GND), L4.2
unnamed: R3.2, R10.1, U12.4 (FB)
unnamed: J1.4 (ID), R13.1, U8.C2 (IO1)
unnamed: EXTRESET.1, R2.2, R13.2, U10.3 (!SR)
unnamed: J1.3 (D+), R28.1, U8.C1 (IO3), USBD+.1
unnamed: L7.1, U12.7 (SW)
unnamed: C21.1, R14.2, U11.1 (OUT), U13.1 (Y0), U13.8 (VCC)
unnamed: D10.A, L9.2
unnamed: J1.2 (D-), R27.1, U8.A1 (IO2), USBD-.1
unnamed: J1.1 (5V), L9.1, U8.A2 (VBUS), USBV.1
unnamed: C19.1, L7.2, R3.1, U12.5 (VOS), U13.2 (Y1)
unnamed: R33.2, U6.5 (G2), U6.6 (D1)
unnamed: R31.1, U6.3 (D2)
NRESET: U10.1 (!RST); also elsewhere on the board
PWR_HIGH: U12.1 (EN); also elsewhere on the board
PWR_MODE: U12.3 (MODE); also elsewhere on the board
PWR_SEL: R4.1, U13.3 (S); also elsewhere on the board
USB_DM: R27.2; also elsewhere on the board
USB_DP: R28.2; also elsewhere on the board
USB_VBUS: C5.1, D10.C, R12.1, U7.1 (VDD), U7.2 (VDD), U14.1 (A), U14.5 (G); also elsewhere on the board
VCC: C3.1, R2.1, R14.1, R15.1, U13.7 (Z); also elsewhere on the board
VUNREG: C9.1, C18.1, C20.1, U10.4 (VCC), U11.4 (EN), U11.6 (IN), U12.8 (VIN), U14.4 (S), U14.6 (C); also elsewhere on the board

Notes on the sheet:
2.5V
80 mA

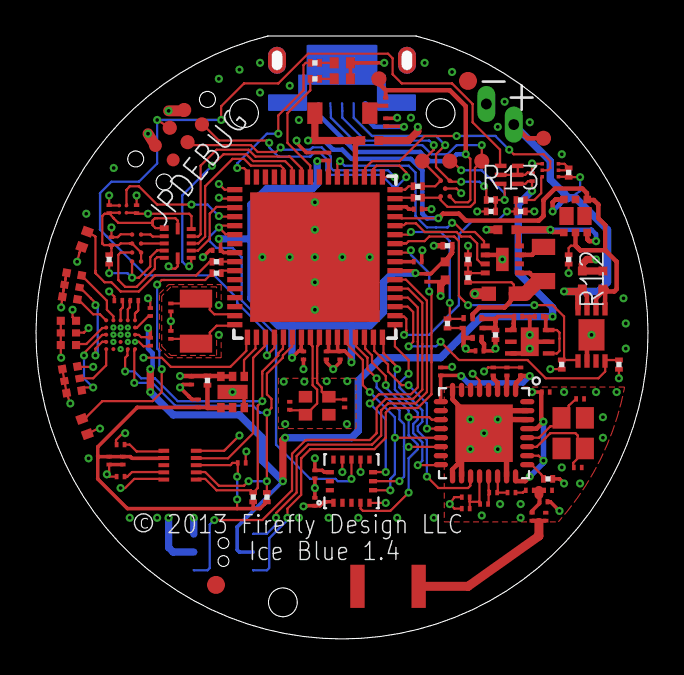
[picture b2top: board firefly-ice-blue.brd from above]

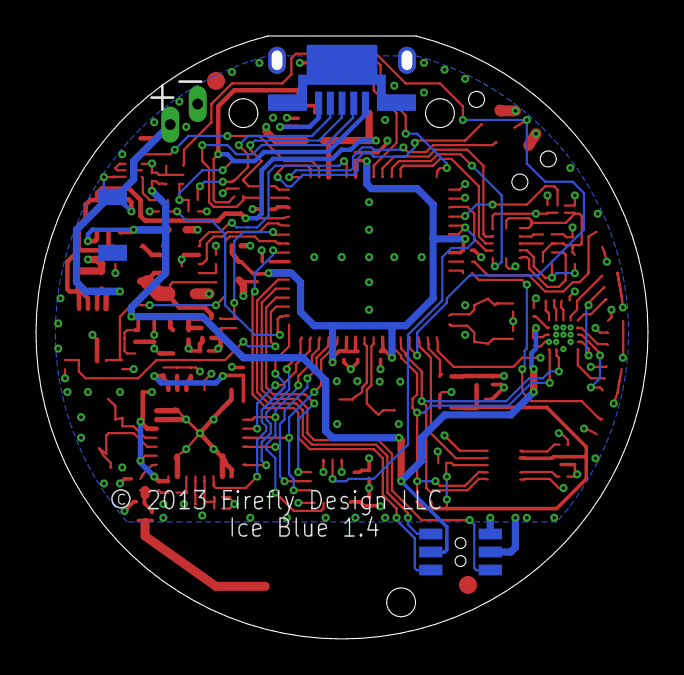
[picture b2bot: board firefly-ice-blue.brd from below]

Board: 4 copper layers, 34.0 x 33.5 mm, 122 parts (3 on the bottom side), 100 nets.

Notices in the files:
firefly-instruments/firefly-instrument-tray.brd:
Copyright Firefly Design LLC
parts and their libraries:
firefly: ©2009 ROFA.cz
